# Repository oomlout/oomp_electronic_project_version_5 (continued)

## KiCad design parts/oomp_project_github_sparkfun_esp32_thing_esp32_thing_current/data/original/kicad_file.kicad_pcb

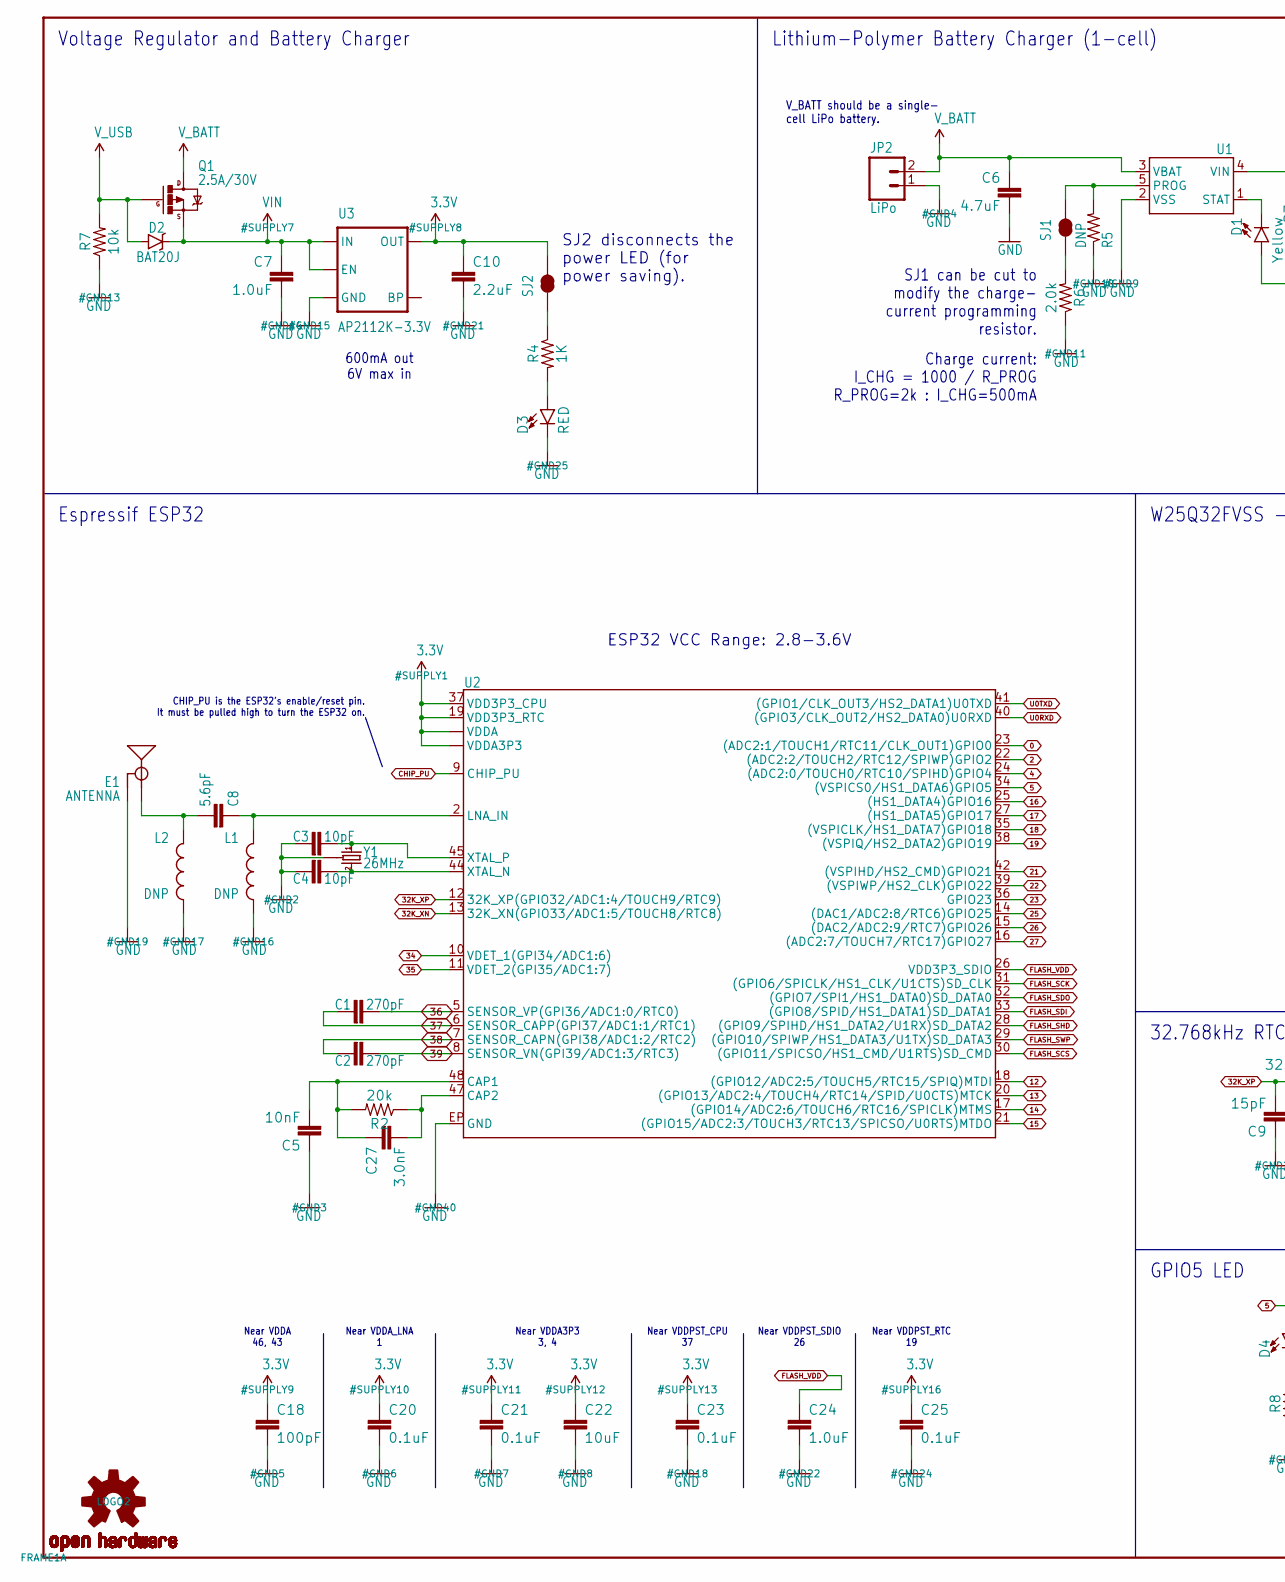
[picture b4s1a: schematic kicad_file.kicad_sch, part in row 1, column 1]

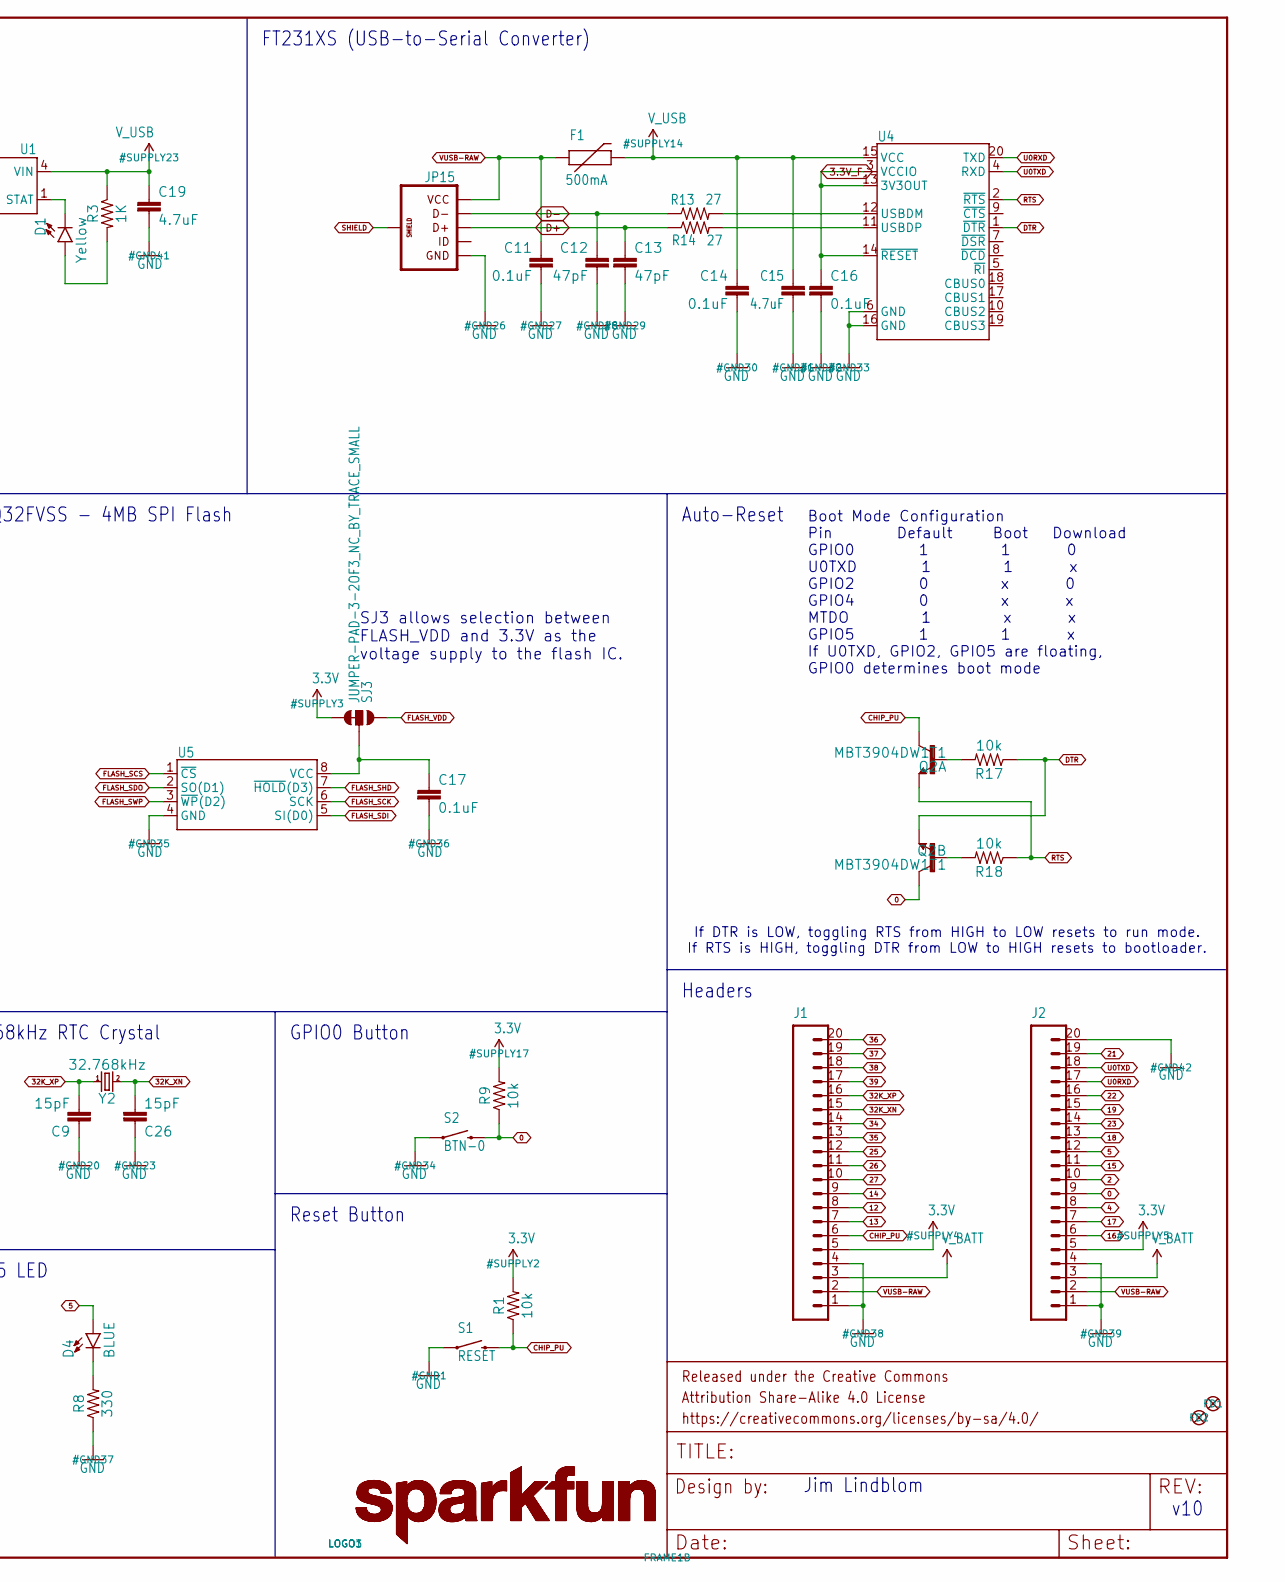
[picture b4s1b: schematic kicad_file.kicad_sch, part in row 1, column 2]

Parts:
C1, C2: 270pF; 0603
C3, C4: 10pF; 0603
C5: 10nF; 0603
C6, C19: 4.7uF; 0603
C7: 1.0uF; 0805
C8: 5.6pF; 0603
C9, C26: 15pF; 0603
C10: 2.2uF; 0603
C11, C14, C16, C17, C20, C21, C23, C25: 0.1uF; 0603
C12, C13: 47pF; 0603
C15: 4.7uF; 0603-CAP
C18: 100pF; 0603
C22: 10uF; 0603
C24: 1.0uF; 0603
C27: 3.0nF; 0603
D1: Yellow; LED-0603
D2: BAT20J; SOD-323
D3: RED; LED-0603
D4: BLUE; LED-0603
E1: ANTENNA; TRACE_ANTENNA_2.4GHZ_25.7MM_TUNED
F1: 500mA; PTC-1206
FD1, FD2: FIDUCIALUFIDUCIAL; MICRO-FIDUCIAL
FRAME1: FRAME-LEDGER; CREATIVE_COMMONS
J1, J2: M20NOSILK; 1X20_NOSILK
JP2: LiPo; JST-2-PTH
JP15: USB_MICROB_PLUGCONN-11752; USB-B-MICRO-SMD_V03
L1, L2: DNP; 0603
LOGO1, LOGO3: SFE_LOGO_NAME.2_INCH; SFE_LOGO_NAME_.2
LOGO2: OSHW-LOGOMINI; OSHW-LOGO-MINI
Q1: 2.5A/30V; SOT23-3
Q2: MBT3904DW1T1; SC70-6
R1, R7, R9, R17, R18: 10k; 0603
R2: 20k; 0603
R3, R4: 1K; 0603
R5: DNP; 1_6W-RES
R6: 2.0k; 0603
R8: 330; 0603
R13, R14: 27; 0603
S1: RESET; TACTILE_SWITCH_SMD_4.6X2.8MM
S2: BTN-0; TACTILE_SWITCH_SMD_4.6X2.8MM
SJ1, SJ2: JUMPER-PAD-2-NC_BY_TRACE; PAD-JUMPER-2-NC_BY_TRACE_YES_SILK
SJ3: JUMPER-PAD-3-2OF3_NC_BY_TRACE_SMALL; PAD-JUMPER-3-2OF3_NC_BY_TRACE_YES_SILK_FULL_BOX
U1: MCP73831; SOT23-5
U2: ESP3212; QFN48-0.4MM
U3: AP2112K-3.3V; SOT23-5
U4: FT231XS; SSOP20_L
U5: W25Q32FVSS; SOIC-8
Y1: 26MHz; CRYSTAL-SMD-3.2X2.5
Y2: 32.768kHz; CRYSTAL-SMD-3.2X1.5MM

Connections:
0: J2.9, Q2.6 (C), R9.1, S2.3 (2), S2.4 (2), U2.23 ((ADC2:1/TOUCH1/RTC11/CLK_OUT1)GPIO0)
2: J2.10, U2.22 ((ADC2:2/TOUCH2/RTC12/SPIWP)GPIO2)
3.3V: C10.1, C18.1, C20.1, C21.1, C22.1, C23.1, C25.1, J1.5, J2.5, R1.2, R9.2, SJ2.2, SJ3.3, U2.1 (VDDA), U2.3 (VDDA3P3), U2.4 (VDDA3P3), U2.19 (VDD3P3_RTC), U2.37 (VDD3P3_CPU), U2.43 (VDDA), U2.46 (VDDA), U3.5 (OUT)
3.3V_F: C16.1, U4.3 (VCCIO), U4.13 (3V3OUT), U4.14 (~RESET)
4: J2.8, U2.24 ((ADC2:0/TOUCH0/RTC10/SPIHD)GPIO4)
5: D4.A, J2.12, U2.34 ((VSPICS0/HS1_DATA6)GPIO5)
12: J1.8, U2.18 ((GPIO12/ADC2:5/TOUCH5/RTC15/SPIQ)MTDI)
13: J1.7, U2.20 ((GPIO13/ADC2:4/TOUCH4/RTC14/SPID/U0CTS)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)
14: J1.9, U2.17 ((GPIO14/ADC2:6/TOUCH6/RTC16/SPICLK)MTMS)
15: J2.11, U2.21 ((GPIO15/ADC2:3/TOUCH3/RTC13/SPICSO/U0RT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)
16: J2.6, U2.25 ((HS1_DATA4)GPIO16)
17: J2.7, U2.27 ((HS1_DATA5)GPIO17)
18: J2.13, U2.35 ((VSPICLK/HS1_DATA7)GPIO18)
19: J2.15, U2.38 ((VSPIQ/HS2_DATA2)GPIO19)
21: J2.19, U2.42 ((VSPIHD/HS2_CMD)GPIO21)
22: J2.16, U2.39 ((VSPIWP/HS2_CLK)GPIO22)
23: J2.14, U2.36 (GPIO23)
25: J1.12, U2.14 ((DAC1/ADC2:8/RTC6)GPIO25)
26: J1.11, U2.15 ((DAC2/ADC2:9/RTC7)GPIO26)
27: J1.10, U2.16 ((ADC2:7/TOUCH7/RTC17)GPIO27)
32K_XN: C26.2, J1.15, U2.13 (32K_XN(GPIO33/ADC1:5/TOUCH8/RTC8)), Y2.P$2 (2)
32K_XP: C9.2, J1.16, U2.12 (32K_XP(GPIO32/ADC1:4/TOUCH9/RTC9)), Y2.P$1 (1)
34: J1.14, U2.10 (VDET_1(GPI34/ADC1:6))
35: J1.13, U2.11 (VDET_2(GPI35/ADC1:7))
36: C1.2, J1.20, U2.5 (SENSOR_VP(GPI36/ADC1:0/RTC0))
37: C1.1, J1.19, U2.6 (SENSOR_CAPP(GPI37/ADC1:1/RTC1))
38: C2.1, J1.18, U2.7 (SENSOR_CAPN(GPI38/ADC1:2/RTC2))
39: C2.2, J1.17, U2.8 (SENSOR_VN(GPI39/ADC1:3/RTC3))
CAP_10N: C5.2, C27.1, R2.2, U2.48 (CAP1)
CHIP_PU: J1.6, Q2.3 (C), R1.1, S1.3 (2), S1.4 (2), U2.9 (CHIP_PU)
D+: C13.1, JP15.D+, R14.1
D-: C12.1, JP15.D-, R13.1
DTR: Q2.1 (E), R17.1, U4.1 (~DTR)
FLASH_SCK: U2.31 ((GPIO6/SPICLK/HS1_CLK/U1CTS)SD_CLK), U5.6 (SCK)
FLASH_SCS: U2.30 ((GPIO11/SPICSO/HS1_CMD/U1RTS)SD_CMD), U5.1 (~CS)
FLASH_SDI: U2.33 ((GPIO8/SPID/HS1_DATA1)SD_DATA1), U5.5 (SI(D0))
FLASH_SDO: U2.32 ((GPIO7/SPI1/HS1_DATA0)SD_DATA0), U5.2 (SO(D1))
FLASH_SHD: U2.28 ((GPIO9/SPIHD/HS1_DATA2/U1RX)SD_DATA2), U5.7 (~HOLD(D3))
FLASH_SWP: U2.29 ((GPIO10/SPIWP/HS1_DATA3/U1TX)SD_DATA3), U5.3 (~WP(D2))
FLASH_VDD: C24.1, SJ3.1, U2.26 (VDD3P3_SDIO)
GND: C3.1, C4.1, C5.1, C6.2, C7.2, C9.1, C10.2, C11.2, C12.2, C13.2, C14.2, C15.2, C16.2, C17.2, C18.2, C19.2, C20.2, C21.2, C22.2, C23.2, C24.2, C25.2, C26.1, D3.C, E1.GND, E1.GND2 (GND), J1.1, J1.4, J2.1, J2.4, J2.20, JP2.1, JP15.GND, L1.2, L2.2, R5.1, R6.1, R7.1, R8.1, S1.1, S1.2 (1), S2.1, S2.2 (1), U1.2 (VSS), U2.EP (GND), U3.2 (GND), U4.6 (GND), U4.16 (GND), U5.4 (GND), Y1.2 (GND), Y1.4 (GND)
LNA_IN: C8.1, L1.1, U2.2 (LNA_IN)
unnamed: D4.C, R8.2
unnamed: D3.A, R4.2
unnamed: R4.1, SJ2.1
unnamed: C27.2, R2.1, U2.47 (CAP2)
unnamed: R13.2, U4.12 (USBDM)
unnamed: R14.2, U4.11 (USBDP)
unnamed: D1.C, U1.1 (STAT)
unnamed: Q2.5 (B), R17.2
unnamed: C17.1, SJ3.2, U5.8 (VCC)
unnamed: Q2.2 (B), R18.2
unnamed: C3.2, U2.45 (XTAL_P), Y1.1
unnamed: R5.2, SJ1.2, U1.5 (PROG)
unnamed: C4.2, U2.44 (XTAL_N), Y1.3 (2)
unnamed: R6.2, SJ1.1
unnamed: D1.A, R3.2
RTS: Q2.4 (E), R18.1, U4.2 (~RTS)
SHIELD: JP15.SHIELD1 (SHIELD), JP15.SHIELD2 (SHIELD), JP15.SHIELD3 (SHIELD)
TRACE_ANT: C8.2, E1.ANT (SIGNAL), L2.1
U0RXD: J2.17, U2.40 ((GPIO3/CLK_OUT2/HS2_DATA0)U0RXD), U4.20 (TXD)
U0TXD: J2.18, U2.41 ((GPIO1/CLK_OUT3/HS2_DATA1)U0TXD), U4.4 (RXD)
VIN: C7.1, D2.C, Q1.2 (S), U3.1 (IN), U3.3 (EN)
VUSB-RAW: C11.1, F1.1, J1.2, J2.2, JP15.VBUS (VCC)
V_BATT: C6.1, J1.3, J2.3, JP2.2, Q1.3 (D), U1.3 (VBAT)
V_USB: C14.1, C15.1, C19.1, D2.A, F1.2, Q1.1 (G), R3.1, R7.2, U1.4 (VIN), U4.15 (VCC)

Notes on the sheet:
SJ2 disconnects the power LED (for power saving).
Near VDDPST_RTC 19
Charge current: I_CHG = 1000 / R_PROG R_PROG=2k : I_CHG=500mA
600mA out 6V max in
Near VDDA_LNA 1
CHIP_PU is the ESP32's enable/reset pin. It must be pulled high to turn the ESP32 on.
Jim Lindblom
Near VDDA3P3 3, 4
Headers
FT231XS (USB-to-Serial Converter)
Lithium-Polymer Battery Charger (1-cell)
SJ3 allows selection between FLASH_VDD and 3.3V as the voltage supply to the flash IC.
Boot Mode Configuration Pin Default Boot Download GPIO0 1 1 0 U0TXD 1 1 x GPIO2 0 x 0 GPIO4 0 x x MTDO 1 x x GPIO5 1 1 x If U0TXD, GPIO2, GPIO5 are floating, GPIO0 determines boot mode
V_BATT should be a single- cell LiPo battery.
Near VDDPST_SDIO 26
GPIO0 Button
v10
Voltage Regulator and Battery Charger
32.768kHz RTC Crystal
W25Q32FVSS - 4MB SPI Flash
Auto-Reset
Reset Button
ESP32 VCC Range: 2.8-3.6V
If DTR is LOW, toggling RTS from HIGH to LOW resets to run mode. If RTS is HIGH, toggling DTR from LOW to HIGH resets to bootloader.
GPIO5 LED
SJ1 can be cut to modify the charge- current programming resistor.
Espressif ESP32
Near VDDPST_CPU 37
Near VDDA 46, 43

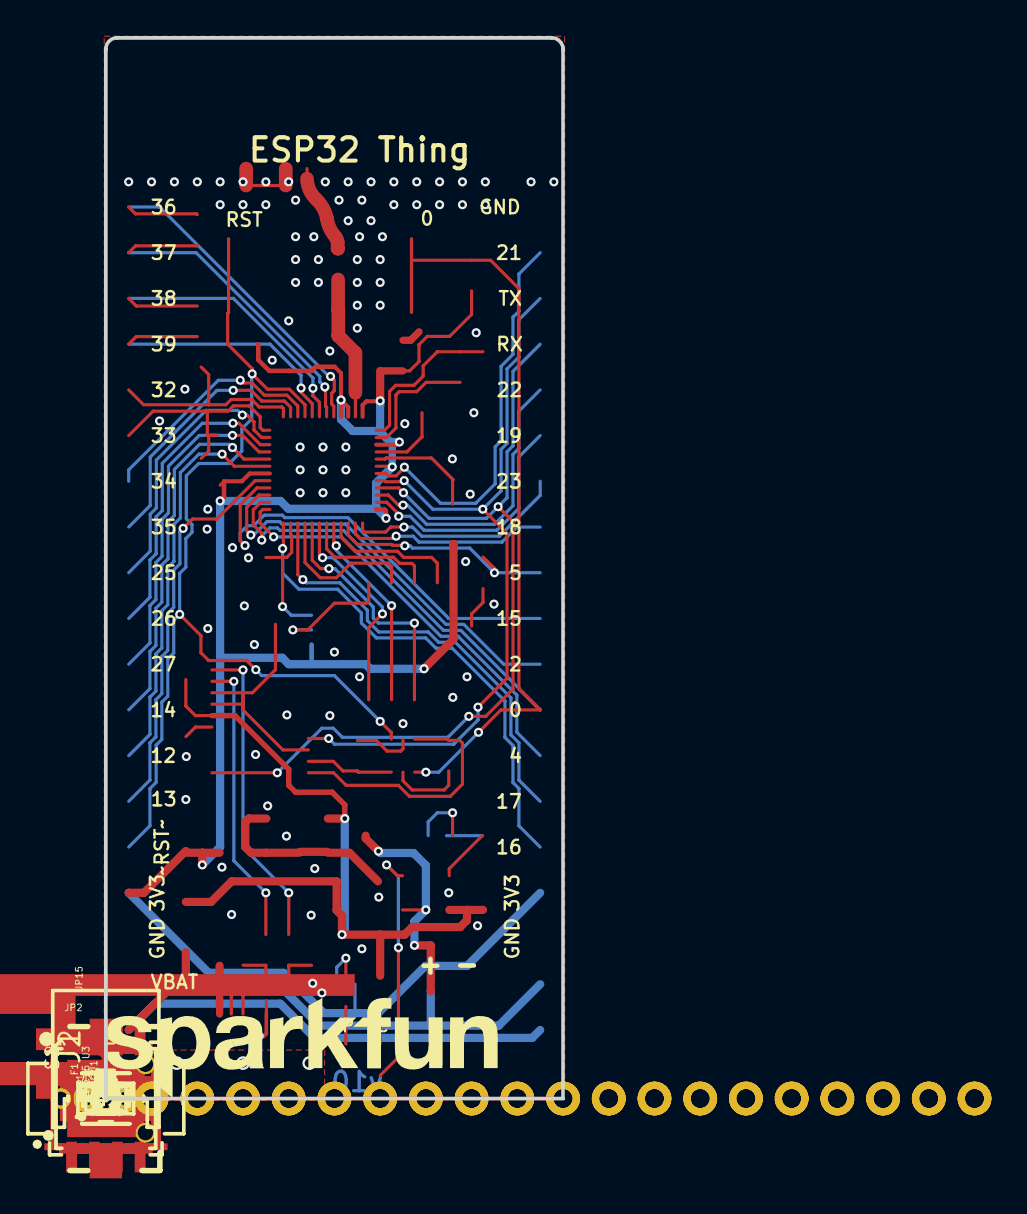
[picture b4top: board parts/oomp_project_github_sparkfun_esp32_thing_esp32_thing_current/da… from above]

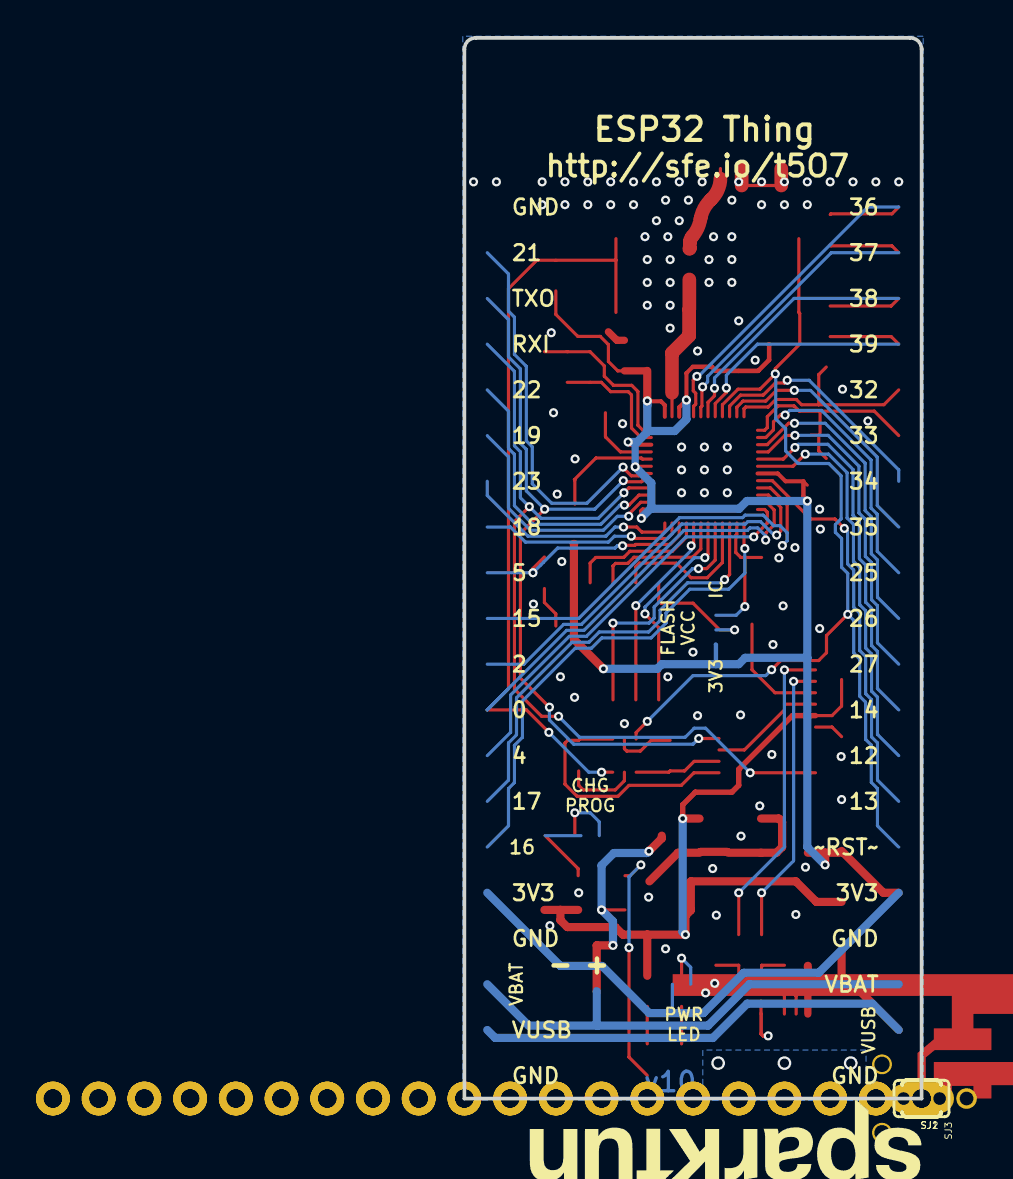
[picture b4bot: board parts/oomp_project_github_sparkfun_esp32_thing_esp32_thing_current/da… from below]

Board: 2 copper layers, 25.4 x 58.9 mm, 72 parts (4 on the bottom side), 66 nets.

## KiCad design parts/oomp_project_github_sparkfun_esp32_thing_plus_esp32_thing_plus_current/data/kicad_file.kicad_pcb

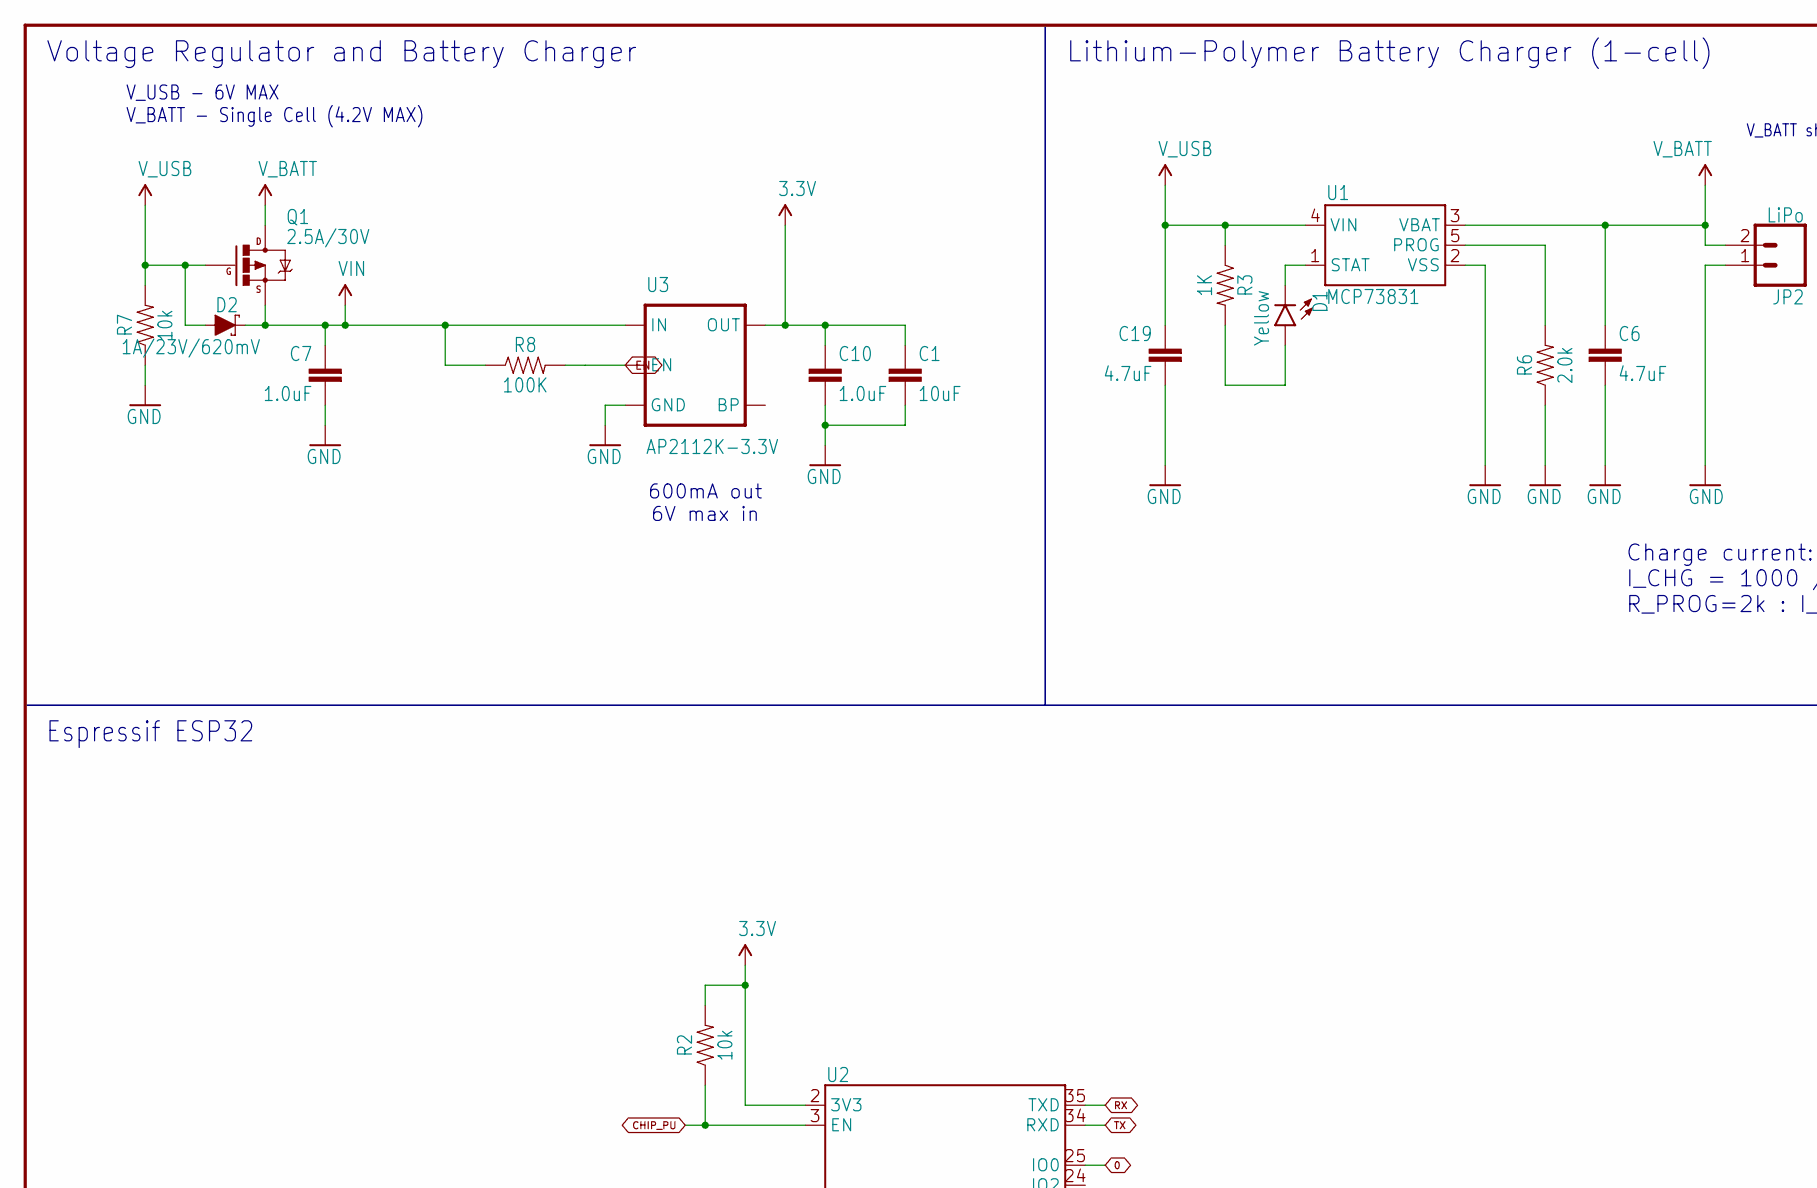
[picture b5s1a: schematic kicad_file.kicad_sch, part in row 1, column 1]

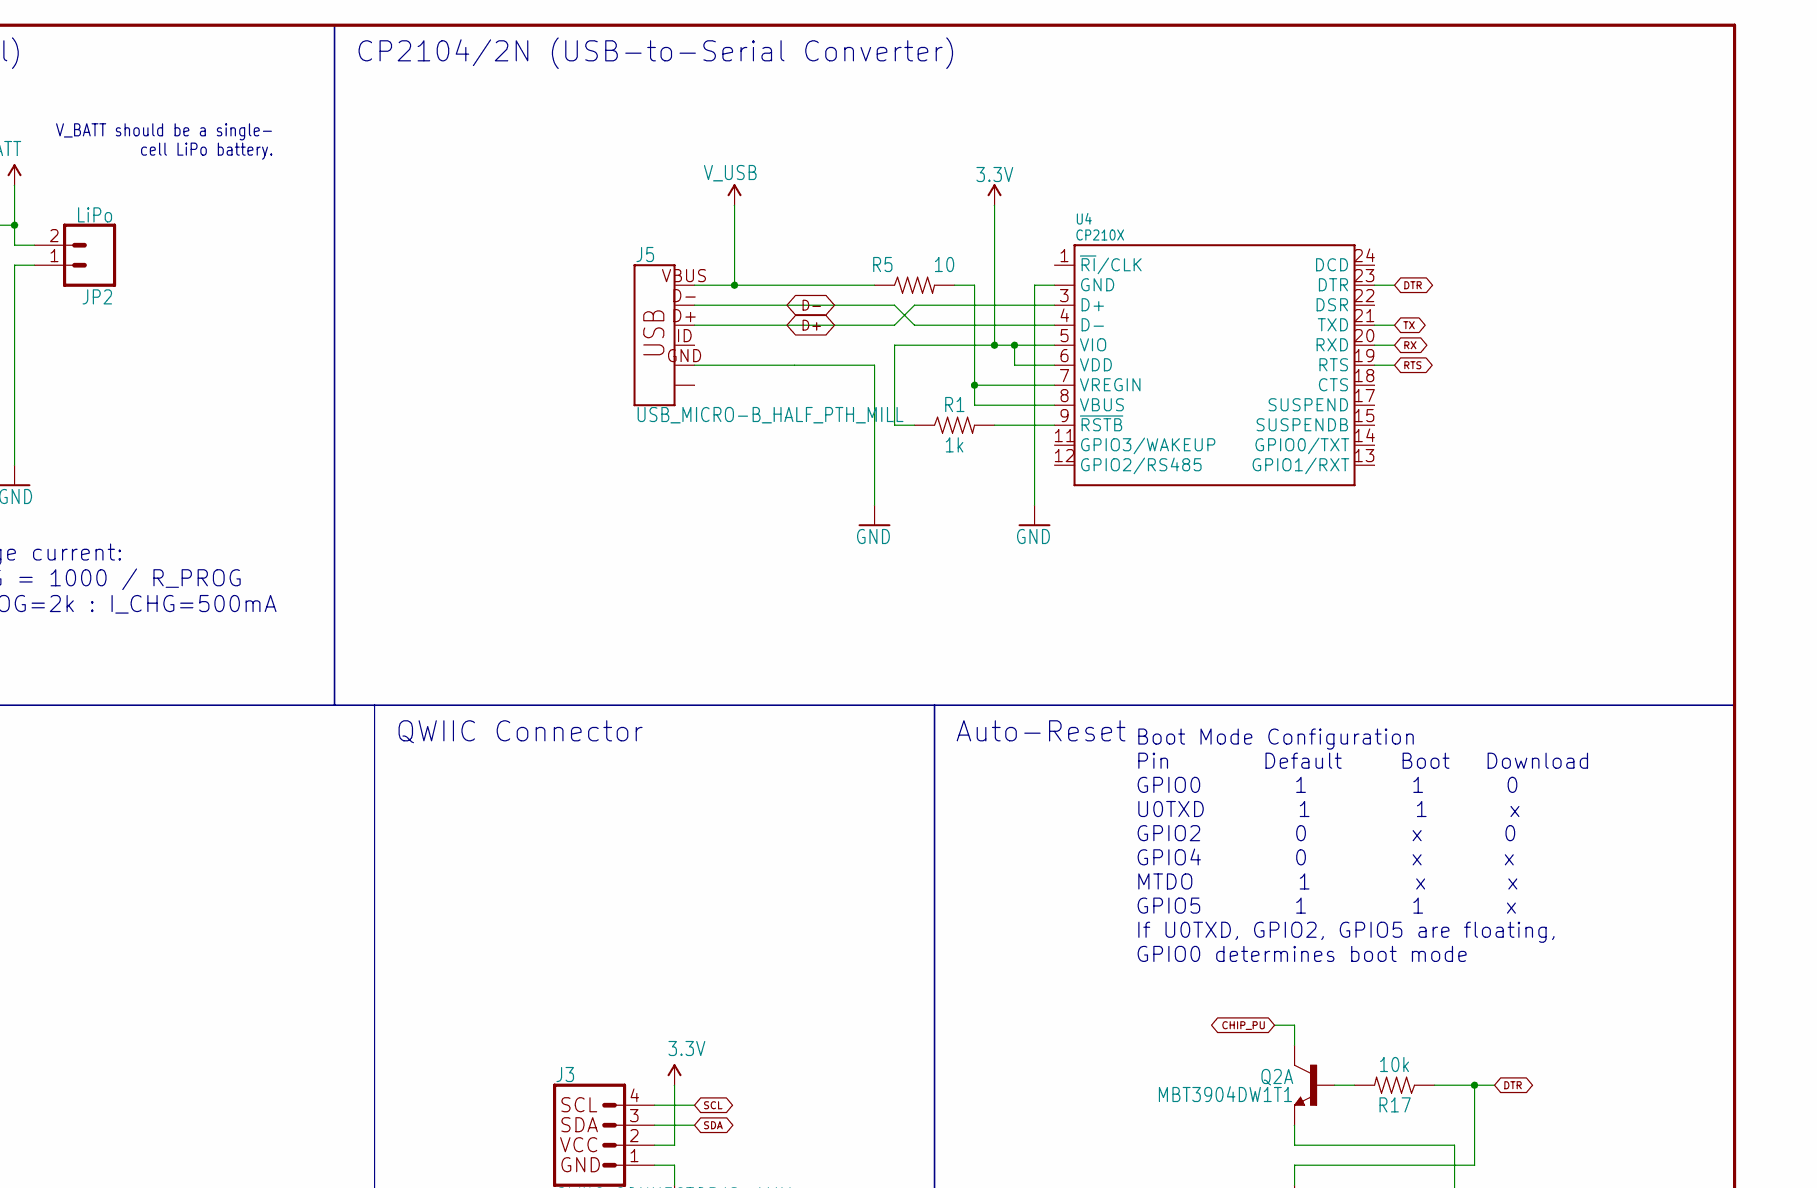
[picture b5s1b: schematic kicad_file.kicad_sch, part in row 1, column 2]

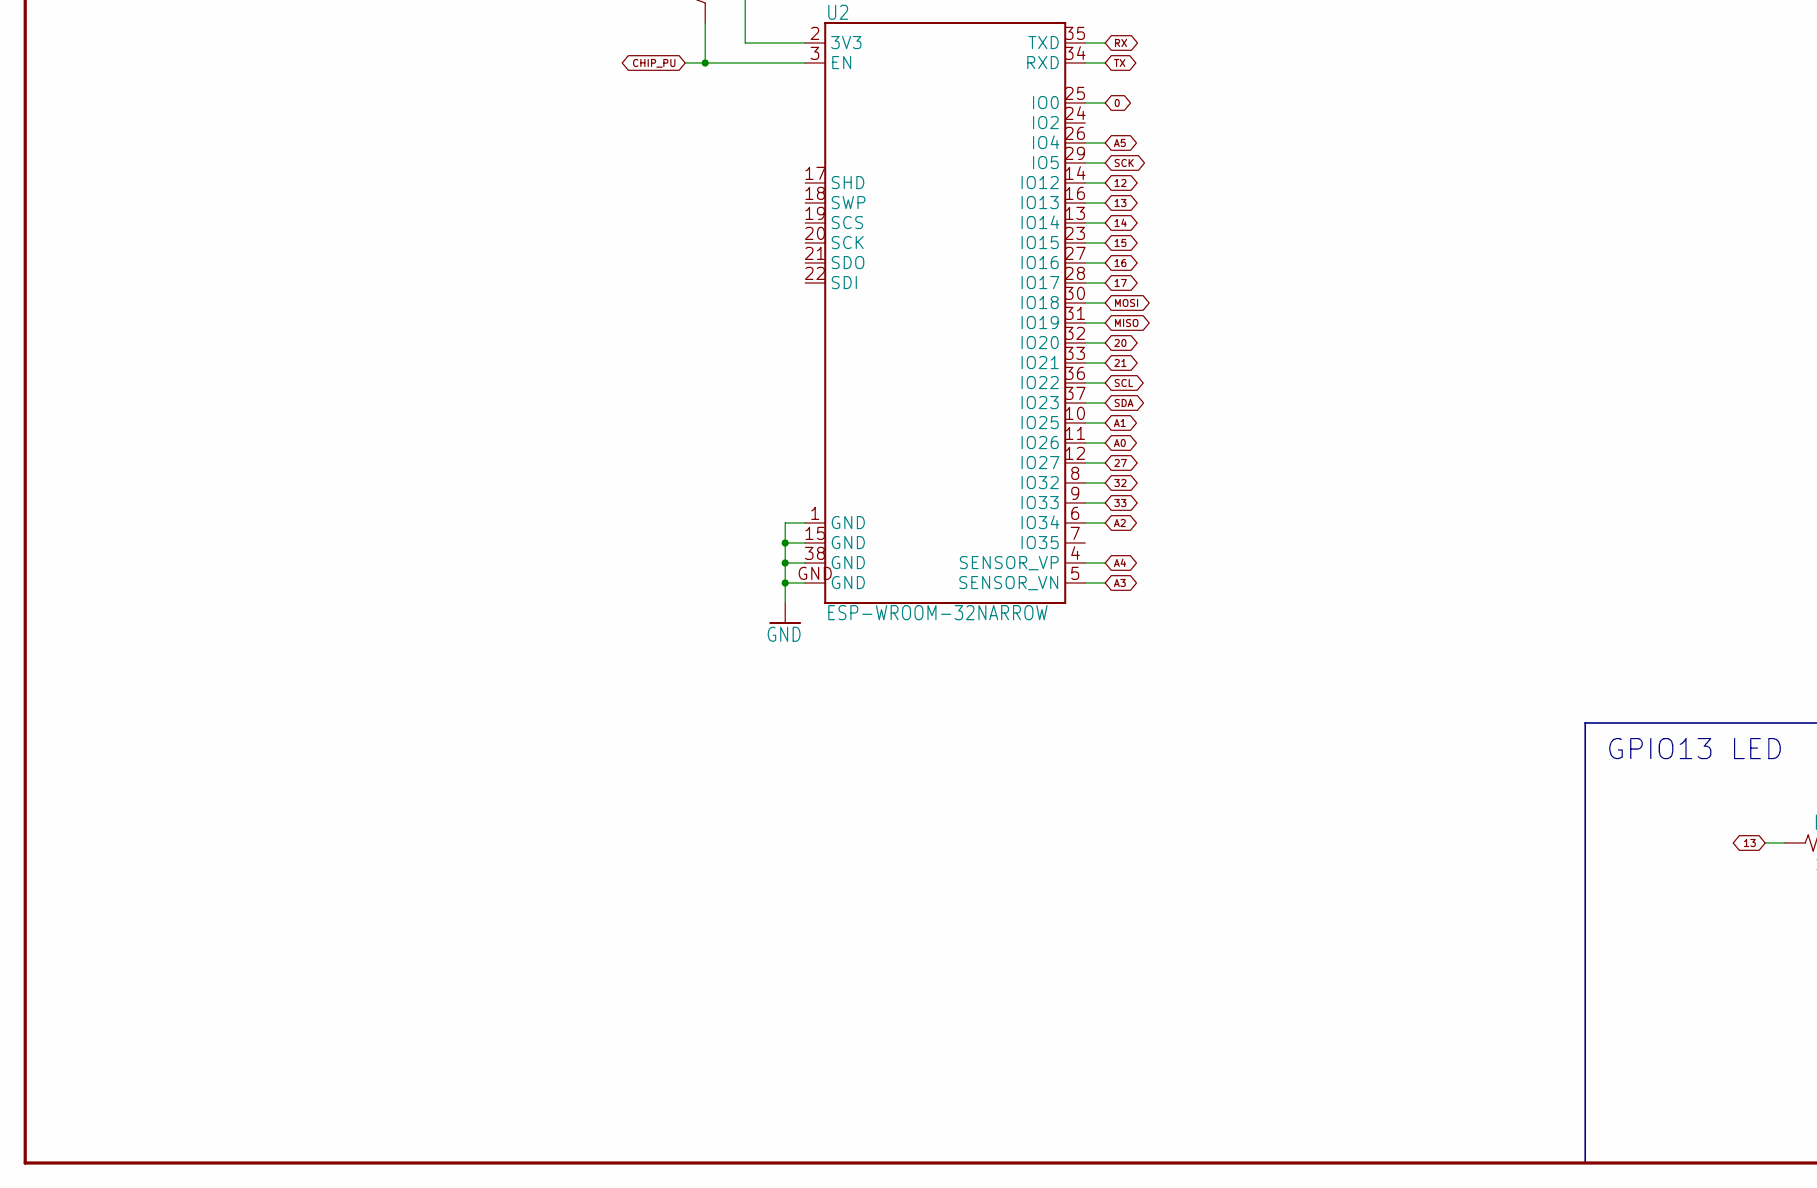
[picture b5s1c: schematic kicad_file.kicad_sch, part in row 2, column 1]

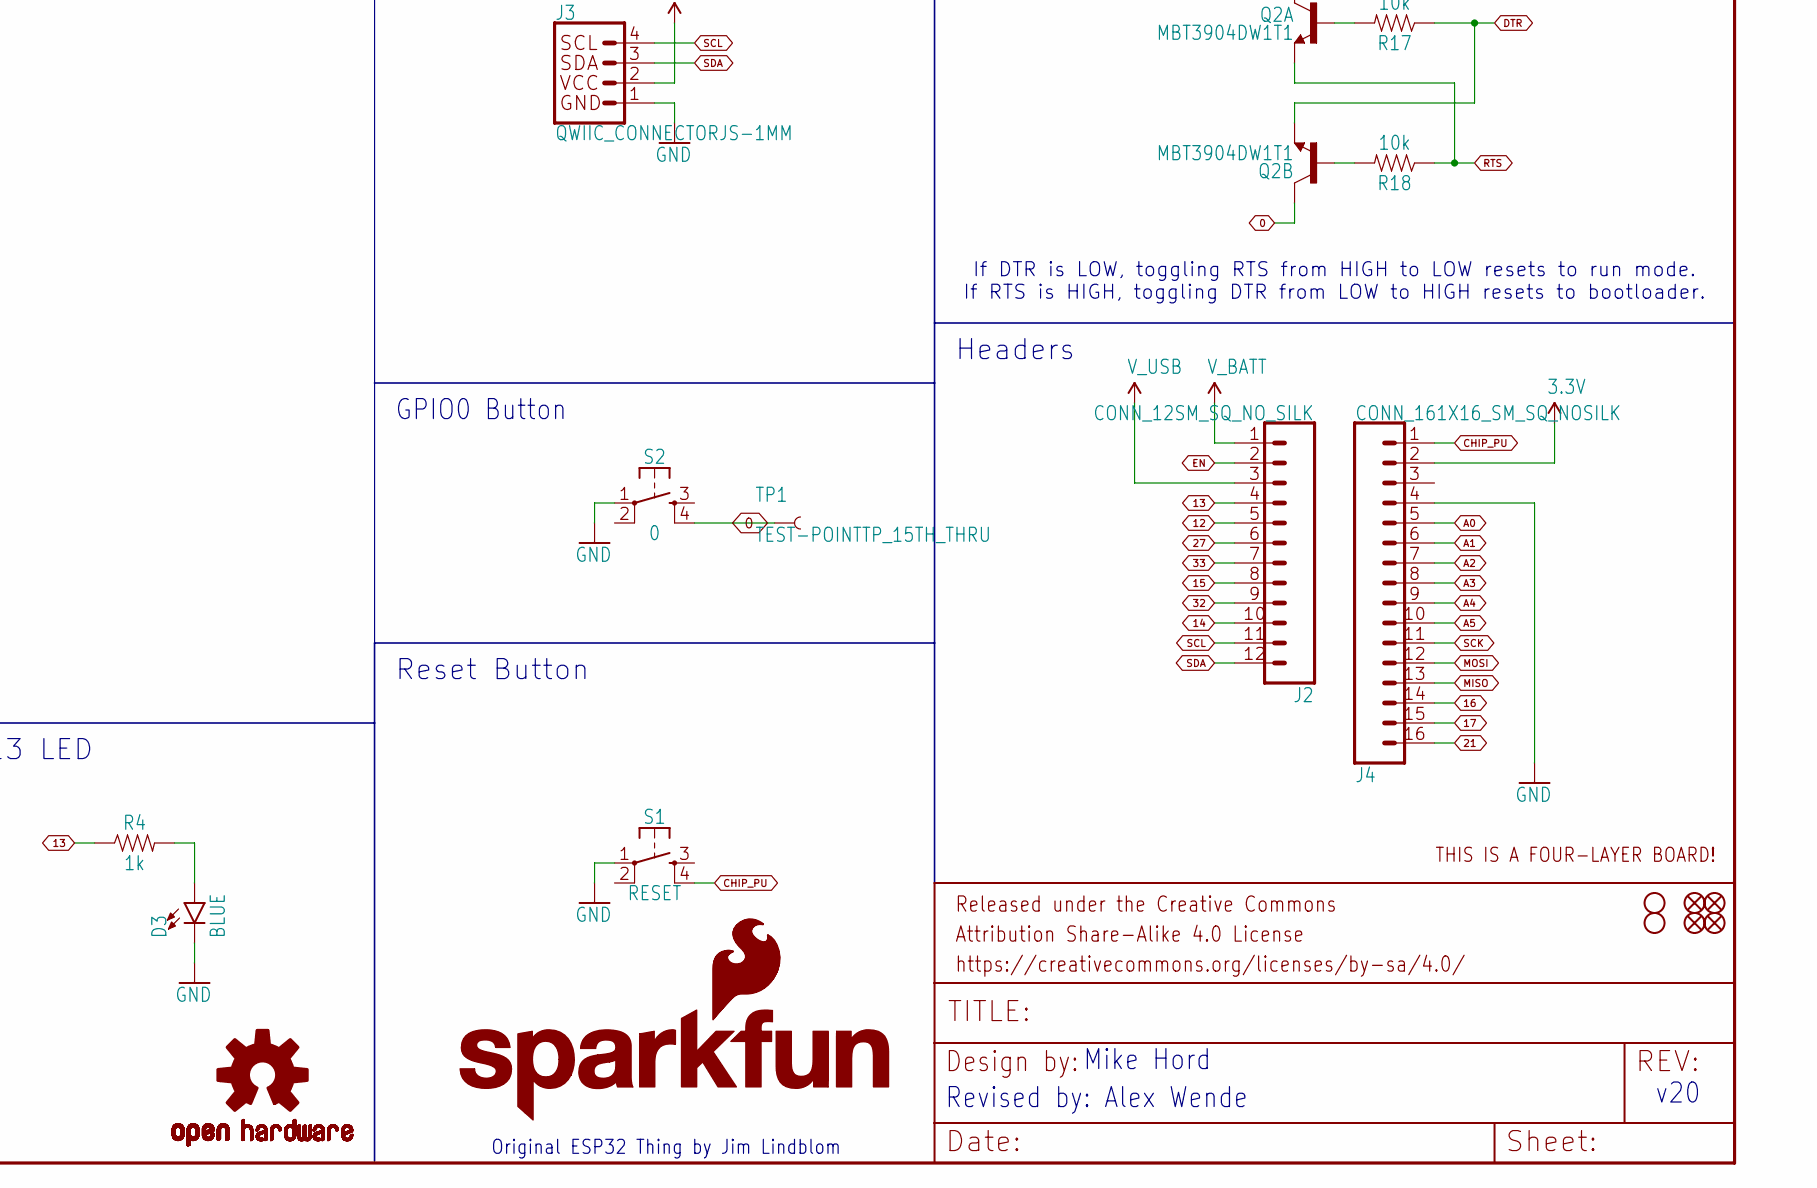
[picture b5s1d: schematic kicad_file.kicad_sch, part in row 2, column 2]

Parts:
C1: 10uF; 0603
C6, C19: 4.7uF; 0603
C7: 1.0uF; 0603
C10: 1.0uF; 0402
D1: Yellow; LED-0603
D2: 1A/23V/620mV; SOD-323
D3: BLUE; LED-0603
FD1, FD2, FD3, FD4: FIDUCIALUFIDUCIAL; FIDUCIAL-MICRO
FRAME1: FRAME-LEDGER; CREATIVE_COMMONS
H1, H2: STAND-OFFTIGHT; STAND-OFF-TIGHT
J2: CONN_12SM_SQ_NO_SILK; 1X12_SM_SQ_NOSILK
J3: QWIIC_CONNECTORJS-1MM; 1X04_1MM_RA
J4: CONN_161X16_SM_SQ_NOSILK; 1X16_SM_SQ_NOSILK
J5: USB_MICRO-B_HALF_PTH_MILL; USB-MICROB-PTH-MILL
JP2: LiPo; JST-2-SMD
LOGO1: SFE_LOGO_FLAME.1_INCH; SFE_LOGO_FLAME_.1
LOGO2: OSHW-LOGOMINI; OSHW-LOGO-MINI
LOGO3: SFE_LOGO_NAME_FLAME.1_INCH; SFE_LOGO_NAME_FLAME_.1
LOGO4: FOUR_LAYER_WARNING
Q1: 2.5A/30V; SOT23-3@1
Q2: MBT3904DW1T1; SC70-6
R1, R4: 1k; 0603
R2, R7, R17, R18: 10k; 0603
R3: 1K; 0603
R5: 10; 0603
R6: 2.0k; 0603
R8: 100K; 0402
S1: RESET; TACTILE_SWITCH_SMD_4.6X2.8MM
S2: 0; TACTILE_SWITCH_SMD_4.6X2.8MM
TP1: TEST-POINTTP_15TH_THRU; TP_15TH
U1: MCP73831; SOT23-5
U2: ESP-WROOM-32NARROW; ESP-WROOM-32-NARROW
U3: AP2112K-3.3V; SOT23-5
U4: CP210X; QFN24

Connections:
0: Q2.6 (C), S2.4, TP1.P$1, U2.25 (IO0)
3.3V: C1.1, C10.1, J3.2, J4.2, R1.1, R2.2, U2.2 (3V3), U3.5 (OUT), U4.5 (VIO), U4.6 (VDD)
12: J2.5, U2.14 (IO12)
13: J2.4, R4.1, U2.16 (IO13)
14: J2.10, U2.13 (IO14)
15: J2.8, U2.23 (IO15)
16: J4.14, U2.27 (IO16)
17: J4.15, U2.28 (IO17)
20: U2.32 (IO20)
21: J4.16, U2.33 (IO21)
27: J2.6, U2.12 (IO27)
32: J2.9, U2.8 (IO32)
33: J2.7, U2.9 (IO33)
A0: J4.5, U2.11 (IO26)
A1: J4.6, U2.10 (IO25)
A2: J4.7, U2.6 (IO34)
A3: J4.8, U2.5 (SENSOR_VN)
A4: J4.9, U2.4 (SENSOR_VP)
A5: J4.10, U2.26 (IO4)
CHG: D1.C, U1.1 (STAT)
CHIP_PU: J4.1, Q2.3 (C), R2.1, S1.4, U2.3 (EN)
D+: J5.D+, U4.3 (D+)
D-: J5.D-, U4.4 (D-)
DTR: Q2.1 (E), R17.1, U4.23 (DTR)
EN: J2.2, R8.2, U3.3 (EN)
GND: C1.2, C6.2, C7.2, C10.2, C19.2, D3.C, J3.1, J4.4, J5.GND, JP2.1 (2), R6.1, R7.1, S1.1, S2.1, U1.2 (VSS), U2.1 (GND), U2.15 (GND), U2.38 (GND), U2.GND, U3.2 (GND), U4.2 (GND), U4.PAD (GND)
MISO: J4.13, U2.31 (IO19)
MOSI: J4.12, U2.30 (IO18)
unnamed: R1.2, U4.9 (~RSTB)
unnamed: D3.A, R4.2
unnamed: R5.2, U4.7 (VREGIN), U4.8 (VBUS)
unnamed: Q2.5 (B), R17.2
unnamed: Q2.2 (B), R18.2
unnamed: R6.2, U1.5 (PROG)
unnamed: D1.A, R3.2
RTS: Q2.4 (E), R18.1, U4.19 (RTS)
RX: U2.35 (TXD), U4.20 (RXD)
SCK: J4.11, U2.29 (IO5)
SCL: J2.11, J3.4, U2.36 (IO22)
SDA: J2.12, J3.3, U2.37 (IO23)
TX: U2.34 (RXD), U4.21 (TXD)
VIN: C7.1, D2.C, Q1.2 (S), R8.1, U3.1 (IN)
V_BATT: C6.1, J2.1, JP2.2 (1), Q1.3 (D), U1.3 (VBAT)
V_USB: C19.1, D2.A, J2.3, J5.VBUS, Q1.1 (G), R3.1, R5.1, R7.2, U1.4 (VIN)

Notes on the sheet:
V_USB - 6V MAX V_BATT - Single Cell (4.2V MAX)
Revised by: Alex Wende
Voltage Regulator and Battery Charger
GPIO13 LED
v20
Original ESP32 Thing by Jim Lindblom
Headers
Reset Button
Charge current: I_CHG = 1000 / R_PROG R_PROG=2k : I_CHG=500mA
Boot Mode Configuration Pin Default Boot Download GPIO0 1 1 0 U0TXD 1 1 x GPIO2 0 x 0 GPIO4 0 x x MTDO 1 x x GPIO5 1 1 x If U0TXD, GPIO2, GPIO5 are floating, GPIO0 determines boot mode
Auto-Reset
If DTR is LOW, toggling RTS from HIGH to LOW resets to run mode. If RTS is HIGH, toggling DTR from LOW to HIGH resets to bootloader.
GPIO0 Button
Mike Hord
Espressif ESP32
V_BATT should be a single- cell LiPo battery.
CP2104/2N (USB-to-Serial Converter)
QWIIC Connector
Lithium-Polymer Battery Charger (1-cell)
600mA out 6V max in
